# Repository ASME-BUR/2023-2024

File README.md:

# Bruin Underwater Robotics (2023-2024)
2023-2024 repository for ASME @ UCLA's Bruin Underwater Robotics Team

## Dependencies
Requires Ubuntu 22.04 + ROS2 Humble

Package dependencies:
- `controller`: `ros-<DISTRO>-control-toolbox`
- `eskf`: `ros-<DISTRO>-robot-localization`, `ros-<DISTRO>-mavros`
- `bur_auv`: `ros-<DISTRO>-navigation2`, `ros-<DISTRO>-behaviortree-cpp`
- `usb_camera_driver`: `ros-<DISTRO>-image-common`
- `drivers`: `pigpio`; see https://github.com/joan2937/pigpio/tree/master

This project contains the following Git submodules: 
- https://github.com/ASME-BUR/bur_rov_msgs
- https://github.com/micro-ROS/micro_ros_setup
- https://github.com/ptrmu/ros2_shared
- https://github.com/klintan/ros2_usb_camera

## Build Instructions
To build all packages: 
1. Install all dependencies: `sudo apt-get install <DEPENDENCIES>`

   i. Follow the instructions at https://github.com/joan2937/pigpio/tree/master for installing `pigpio`
3. Clone this repository: `git clone https://github.com/ASME-BUR/2023-2024.git`
4. Initialize Git submodules: `cd 2023-2024 && git submodule init && git submodule update`
5. Build ROS packages: `cd ros2_ws && colcon build --symlink-install`

## Run Instructions
To run as an AUV, run:
1. On Raspberry Pi (via SSH):

   i. Launch ROS nodes: `ros2 launch bur_rov rov.launch.py`
3. On Jetson Orin (via SSH):

   i. Launch ZED node: `ros2 launch bur_vision zed.launch.py`

   ii. Run YOLO: `ros2 run yolo yolo`

### Micro-Ros-Agent
To Run Micro-Ros-Agent separately, enter:

```
ros2 run micro_ros_agent micro_ros_agent serial --dev /dev/ttyACM0
```

- Serial indicates the transport type
- --dev is the port

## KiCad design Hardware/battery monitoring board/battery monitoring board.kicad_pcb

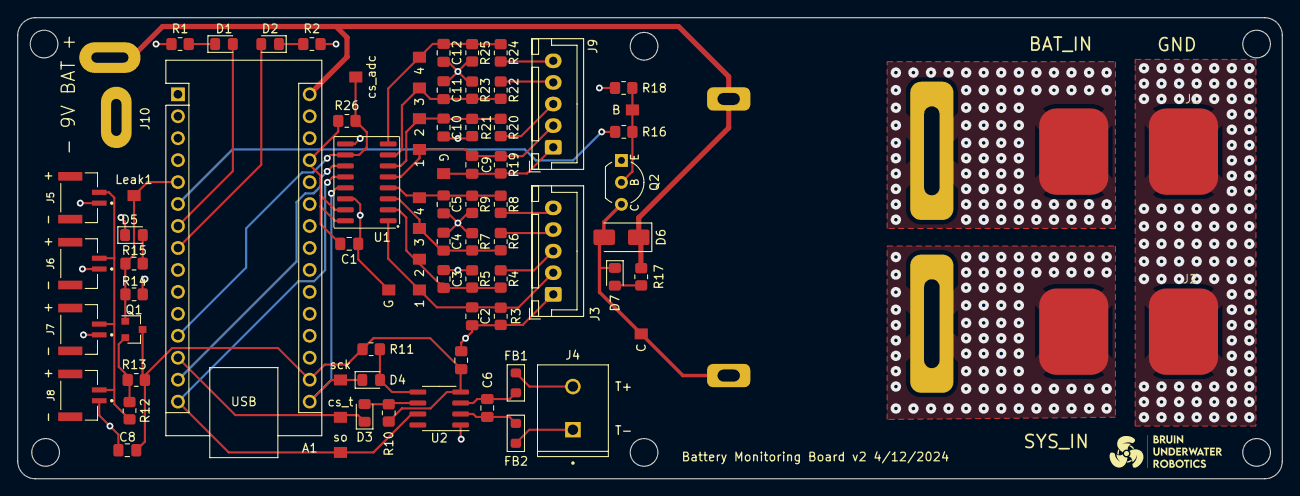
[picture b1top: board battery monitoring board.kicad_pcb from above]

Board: 2 copper layers, 146.3 x 53.3 mm, 80 parts (0 on the bottom side), 43 nets.

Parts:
3V7A1, 3V7B1, 7V4A1, 7V4B1, 11V1A1, 11V1B1, 14V8A1, 14V8B1: TestPoint; TestPoint_Pad_06
A1: Arduino_Nano_v3.x; Arduino_Nano
C1: 100nF; C_0805_2012Metric_Pad1.18x1.45mm_HandSolder
C2, C3, C4, C5, C9, C10, C11, C12: 10nF; C_0805_2012Metric_Pad1.18x1.45mm_HandSolder
C6: 0.01u; C_0805_2012Metric_Pad1.18x1.45mm_HandSolder
C7, C8: 10u; C_0805_2012Metric_Pad1.18x1.45mm_HandSolder
D1, D2: Green LED; D_0805_2012Metric_Pad1.15x1.40mm_HandSolder
D3, D4: D; D_0805_2012Metric_Pad1.15x1.40mm_HandSolder
D5, D7: LED; D_0805_2012Metric_Pad1.15x1.40mm_HandSolder
D6: 1N4007; D_SMA
FB1, FB2: FerriteBead; Ferrite_0805_2012Metric_Pad1.05x1.20mm_BigPads
J1, J2: Conn_01x02; Power Supply Pads
J3, J9: S5B-XH-A; JST_XH_B5B-XH-A_1x05_P2.50mm_Vertical
J4: Conn_01x02; TE_282836-2
J5, J6, J7, J8: Conn_01x02; JST_BM02B-GHS-TBT_LF__SN_
J10: - 9V BAT +; DEANS
K1: Relay_SPST-NO; Relay
Leak1: TestPoint; TestPoint_Pad_06
Q1: PNP; SOT-23
Q2: PN2222A; TO-92_Inline_Wide_EBC
R1, R2: 150; R_0805_2012Metric_Pad1.20x1.40mm_HandSolder
R3, R6, R19, R22: 20k; R_0805_2012Metric_Pad1.20x1.40mm_HandSolder
R4, R5, R7, R9, R10, R11, R20, R21, R23, R25, R26: 10k; R_0805_2012Metric_Pad1.20x1.40mm_HandSolder
R8, R24: 30k; R_0805_2012Metric_Pad1.20x1.40mm_HandSolder
R12, R14: 1k; R_0805_2012Metric_Pad1.20x1.40mm_HandSolder
R13: 27k; R_0805_2012Metric_Pad1.20x1.40mm_HandSolder
R15: 100; R_0805_2012Metric_Pad1.20x1.40mm_HandSolder
R16: 220; R_0805_2012Metric_Pad1.20x1.40mm_HandSolder
R17: 360; R_0805_2012Metric_Pad1.20x1.40mm_HandSolder
R18: 4.7k; R_0805_2012Metric_Pad1.20x1.40mm_HandSolder
TP1, TP2, TP4: TestPoint; TestPoint_Pad_06
U1: MCP3008; SOIC-16_3.9x9.9mm_P1.27mm
U2: MAX31855KASA; SOIC-8_3.9x4.9mm_P1.27mm
cs_adc1: TestPoint; TestPoint_Pad_06
cs_temp1: TestPoint; TestPoint_Pad_06
ground1: TestPoint; TestPoint_Pad_06
sck1: TestPoint; TestPoint_Pad_06
so1: TestPoint; TestPoint_Pad_06

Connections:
+3V3: A1.17 (3V3), C7.1, C8.1, Q1.3 (E), R10.2, R11.1, R13.1, U2.4 (V_CC)
+5V: A1.27 (+5V), C1.1, R26.2, U1.15 (Vref), U1.16 (Vdd)
+9V: A1.30 (VIN), D6.1 (K), J10.1, K1.A1, R17.1
/e-switch/BATTERY_IN: J1.2, K1.14
/e-switch/MCU_OUTPUT: A1.6 (D3), R16.1
/e-switch/SYSTEM_POWER: J2.1, K1.13
/leak sensor/LEAK_SIGNAL: A1.5 (D2), Leak1.1, Q1.1 (C), R14.1, R15.1
/leak sensor/PROBE: J5.2, J6.2, J7.2, J8.2, R12.1
/temp sensor/cs: A1.13 (D10), D3.1 (K), cs_temp1.1
/temp sensor/sck: A1.16 (D13), D4.1 (K), U1.13 (CLK), sck1.1
/temp sensor/so: A1.15 (D12), U1.12 (Dout), U2.7 (SO), so1.1
/voltage monitor2/7V4: J9.3, R20.2
/voltage monitor2/11V1: J9.4, R22.2
/voltage monitor2/14V8: J9.5, R24.2
/voltage monitor2/OUT1: 3V7B1.1, C9.1, J9.2, R19.1, U1.5 (CH4)
/voltage monitor2/OUT2: 7V4B1.1, C10.1, R20.1, R21.1, U1.6 (CH5)
/voltage monitor2/OUT3: 11V1B1.1, C11.1, R22.1, R23.1, U1.7 (CH6)
/voltage monitor2/OUT4: 14V8B1.1, C12.1, R24.1, R25.2, U1.8 (CH7)
/voltage monitor/7V4: J3.3, R4.2
/voltage monitor/11V1: J3.4, R6.2
/voltage monitor/14V8: J3.5, R8.2
/voltage monitor/OUT1: 3V7A1.1, C2.1, J3.2, R3.1, U1.1 (CH0)
/voltage monitor/OUT2: 7V4A1.1, C3.1, R4.1, R5.1, U1.2 (CH1)
/voltage monitor/OUT3: 11V1A1.1, C4.1, R6.1, R7.1, U1.3 (CH2)
/voltage monitor/OUT4: 14V8A1.1, C5.1, R8.1, R9.2, U1.4 (CH3)
GND: A1.4 (GND), A1.29 (GND), C1.2, C2.2, C3.2, C4.2, C5.2, C7.2, C8.2, C9.2, C10.2, C11.2, C12.2, D5.1 (K), J1.1, J2.2, J3.1, J5.1, J6.1, J7.1, J8.1, J9.1, J10.2, Q2.1 (E), R1.1, R2.1, R3.2, R5.2, R7.2, R9.1, R14.2, R18.2, R19.2, R21.2, R23.2, R25.1, TP4.1, U1.9 (DGND), U1.14 (AGND), U2.1 (GND), ground1.1
unnamed: A1.7 (D4), D1.2 (A)
unnamed: A1.8 (D5), D2.2 (A)
unnamed: A1.12 (D9), R26.1, U1.10 (~CS/SHDN), cs_adc1.1
unnamed: A1.14 (D11), U1.11 (Din)
unnamed: D1.1 (K), R1.2
unnamed: D2.1 (K), R2.2
unnamed: D3.2 (A), R10.1, U2.6 (~CS)
unnamed: D4.2 (A), R11.2, U2.5 (SCK)
unnamed: D5.2 (A), R15.2
unnamed: D6.2 (A), D7.1 (K), K1.A2, Q2.3 (C), TP2.1
unnamed: D7.2 (A), R17.2
unnamed: FB2.1, J4.1
unnamed: FB1.1, J4.2
unnamed: Q1.2 (B), R12.2, R13.2
unnamed: Q2.2 (B), R16.2, R18.1, TP1.1
unnamed: C6.1, FB1.2, U2.3 (T+)
unnamed: C6.2, FB2.2, U2.2 (T-)

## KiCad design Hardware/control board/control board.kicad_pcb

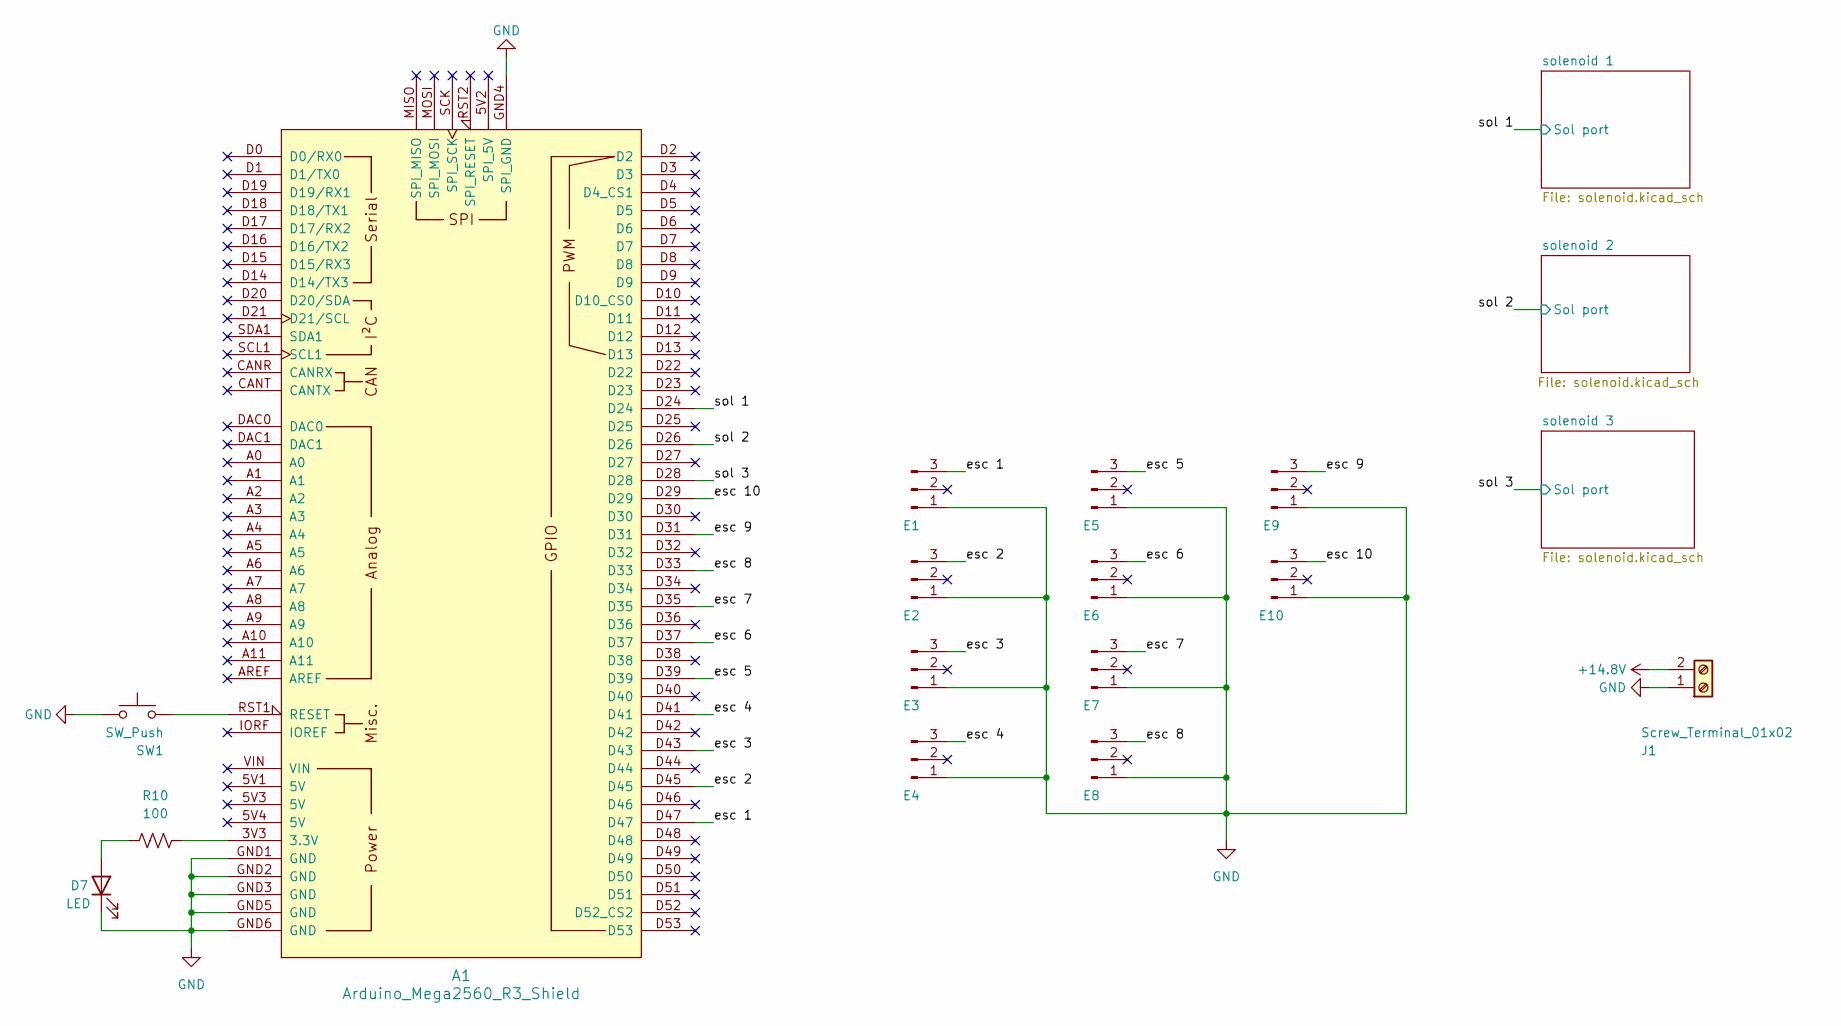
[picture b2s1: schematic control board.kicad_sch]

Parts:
A1: Arduino_Mega2560_R3_Shield; Arduino_Due_Shield
D7: LED; LED_D3.0mm_Clear
E1, E2, E3, E4, E5, E6, E7, E8, E9, E10: Conn_01x03_Pin; PinHeader_1x03_P2.54mm_Vertical
J1: Screw_Terminal_01x02; TE_282836-2
R10: 100; R_0805_2012Metric
SW1: SW_Push; SW_PUSH_6mm

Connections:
+14.8V: J1.2; also elsewhere on the board
/esc 1: A1.D47, E1.3
/esc 2: A1.D45, E2.3
/esc 3: A1.D43, E3.3
/esc 4: A1.D41, E4.3
/esc 5: A1.D39, E5.3
/esc 6: A1.D37, E6.3
/esc 7: A1.D35, E7.3
/esc 8: A1.D33, E8.3
/esc 9: A1.D31, E9.3
/esc 10: A1.D29, E10.3
/sol 1: A1.D24; also elsewhere on the board
/sol 2: A1.D26; also elsewhere on the board
/sol 3: A1.D28; also elsewhere on the board
GND: A1.GND1 (GND), A1.GND2 (GND), A1.GND3 (GND), A1.GND4 (SPI_GND), A1.GND5 (GND), A1.GND6 (GND), D7.1 (K), E1.1, E2.1, E3.1, E4.1, E5.1, E6.1, E7.1, E8.1, E9.1, E10.1, J1.1, SW1.1; also elsewhere on the board
unnamed: A1.3V3 (3.3V), R10.2
unnamed: A1.RST1 (RESET), SW1.2
unnamed: D7.2 (A), R10.1

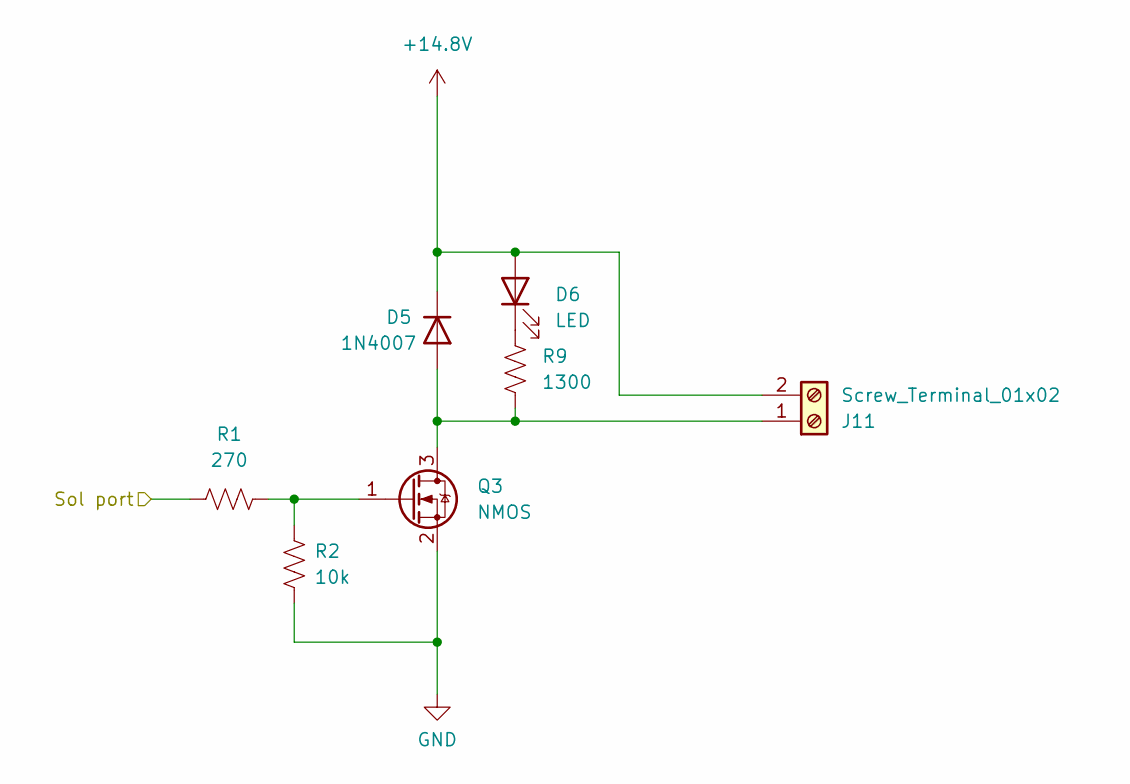
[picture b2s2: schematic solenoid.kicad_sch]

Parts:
D5: 1N4007; D_DO-41_SOD81_P10.16mm_Horizontal
D6: LED; LED_D3.0mm
J11: Screw_Terminal_01x02; TE_282836-2
Q3: NMOS; SOT-23
R1: 270; R_0805_2012Metric
R2: 10k; R_0805_2012Metric
R9: 1300; R_0805_2012Metric

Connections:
+14.8V: D5.1 (K), D6.2 (A), J11.2; also elsewhere on the board
/sol 1: R1.1; also elsewhere on the board
GND: Q3.2 (S), R2.2; also elsewhere on the board
unnamed: D5.2 (A), J11.1, Q3.3 (D), R9.2
unnamed: D6.1 (K), R9.1

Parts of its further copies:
D1, D3: 1N4007; D_DO-41_SOD81_P10.16mm_Horizontal
D2, D4: LED; LED_D3.0mm
J9, J10: Screw_Terminal_01x02; TE_282836-2
Q1, Q2: NMOS; SOT-23
R3, R7: 270; R_0805_2012Metric
R4, R8: 10k; R_0805_2012Metric
R5, R6: 1300; R_0805_2012Metric

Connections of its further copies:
+14.8V: D1.1 (K), D2.2 (A), D3.1 (K), D4.2 (A), J9.2, J10.2; also elsewhere on the board
/sol 2: R3.1; also elsewhere on the board
/sol 3: R7.1; also elsewhere on the board
GND: Q1.2 (S), Q2.2 (S), R4.2, R8.2; also elsewhere on the board
unnamed: D1.2 (A), J9.1, Q1.3 (D), R5.2
unnamed: D2.1 (K), R5.1
unnamed: D3.2 (A), J10.1, Q2.3 (D), R6.2
unnamed: D4.1 (K), R6.1
unnamed: Q2.1 (G), R3.2, R4.1

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
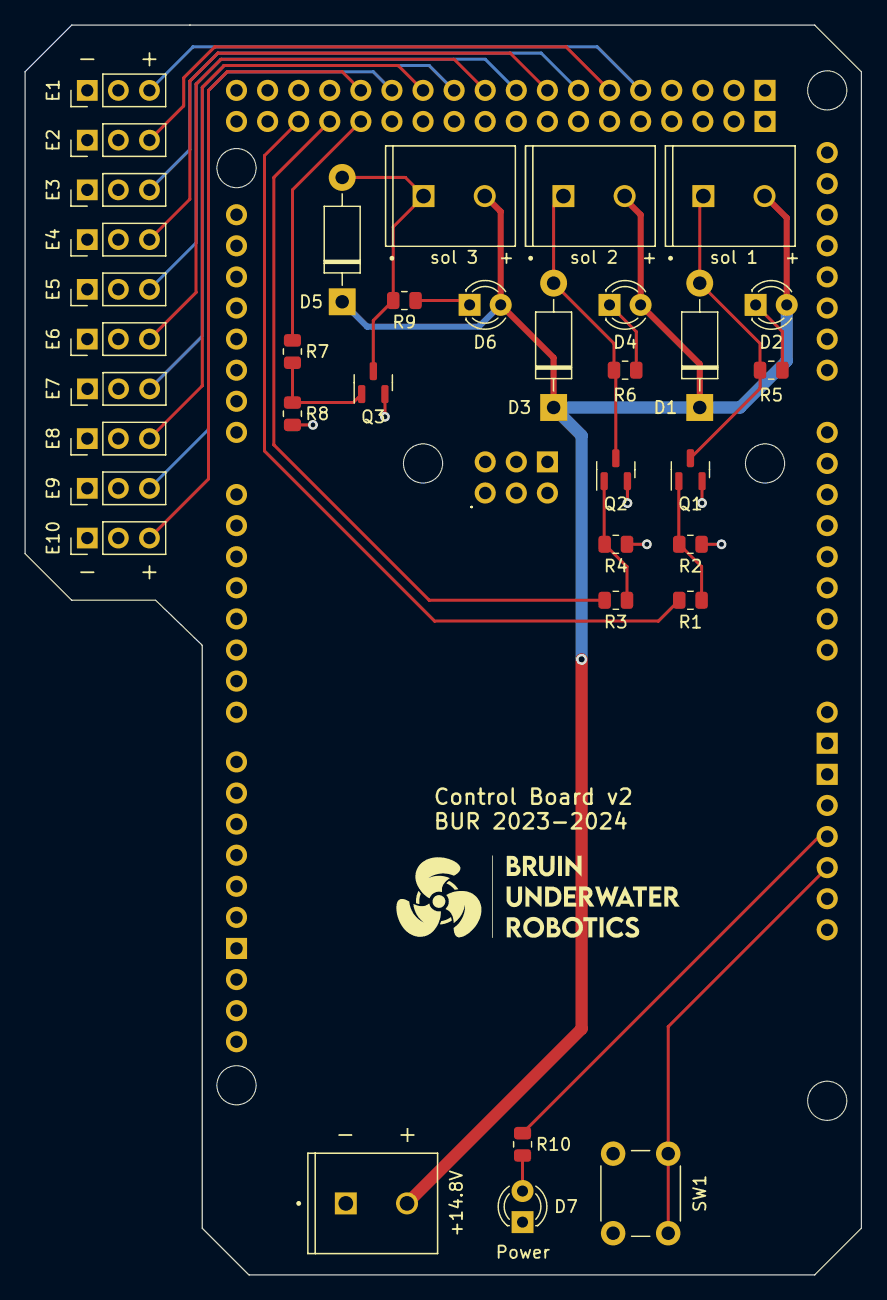
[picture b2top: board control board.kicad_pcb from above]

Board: 2 copper layers, 68.3 x 102.1 mm, 36 parts (0 on the bottom side), 27 nets.

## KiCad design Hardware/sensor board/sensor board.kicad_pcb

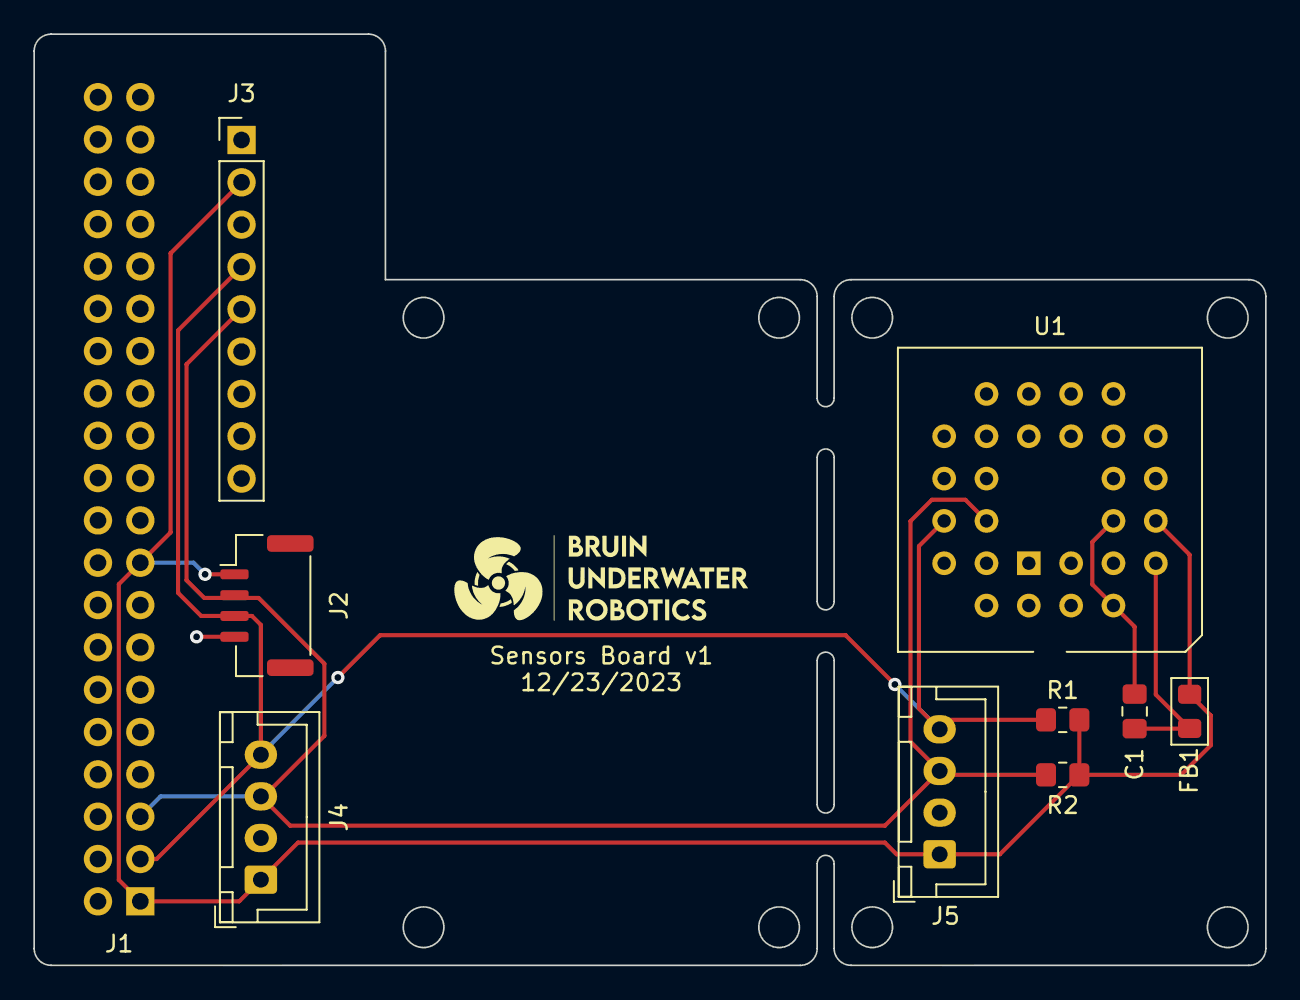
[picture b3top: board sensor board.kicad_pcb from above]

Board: 2 copper layers, 73.9 x 55.9 mm, 10 parts (1 on the bottom side), 5 nets.

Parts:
C1: 470nF; C_0805_2012Metric_Pad1.18x1.45mm_HandSolder
FB1: 600R@100MHz, 200mA; Ferrite_0805_2012Metric_Pad1.15x1.40mm_BigPads
J1: Raspberry_Pi_2_3; PinSocket_2x20_P2.54mm_Vertical
J2: Bar30; JST_GH_BM04B-GHS-TBT_1x04-1MP_P1.25mm_Vertical
J3: LPS331AP; PinHeader_1x09_P2.54mm_Vertical
J4, J5: Conn_01x04_Pin; JST_XH_B4B-XH-A_1x04_P2.50mm_Vertical
R1, R2: 2.7k; R_0805_2012Metric_Pad1.20x1.40mm_HandSolder
U1: MTi_3; PLCC-28_THT-Socket

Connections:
+3.3V: FB1.1, J1.1 (3V3), J1.17 (3V3), J2.1 (3.3V), J3.2 (VIN), J4.1, J5.1, R1.2, R2.2, U1.7 (VDDIO)
/SCL: J1.5 (SCL/GPIO3), J2.2 (SCL), J3.5 (SCL), J4.3, J5.3, R2.1, U1.24 (I2C_SCL)
/SDA: J1.3 (SDA/GPIO2), J2.3 (SDA), J3.4 (SDA), J4.4, J5.4, R1.1, U1.23 (I2C_SDA)
GND: C1.1, J1.6 (GND), J1.9 (GND), J1.14 (GND), J1.20 (GND), J1.25 (GND), J1.30 (GND), J1.34 (GND), J1.39 (GND), J2.4 (GND), J3.3 (GND), J4.2, J5.2, U1.4 (GND), U1.8 (GND), U1.13 (GND), U1.25 (GND)
unnamed: C1.2, FB1.2, U1.5 (VDDA)

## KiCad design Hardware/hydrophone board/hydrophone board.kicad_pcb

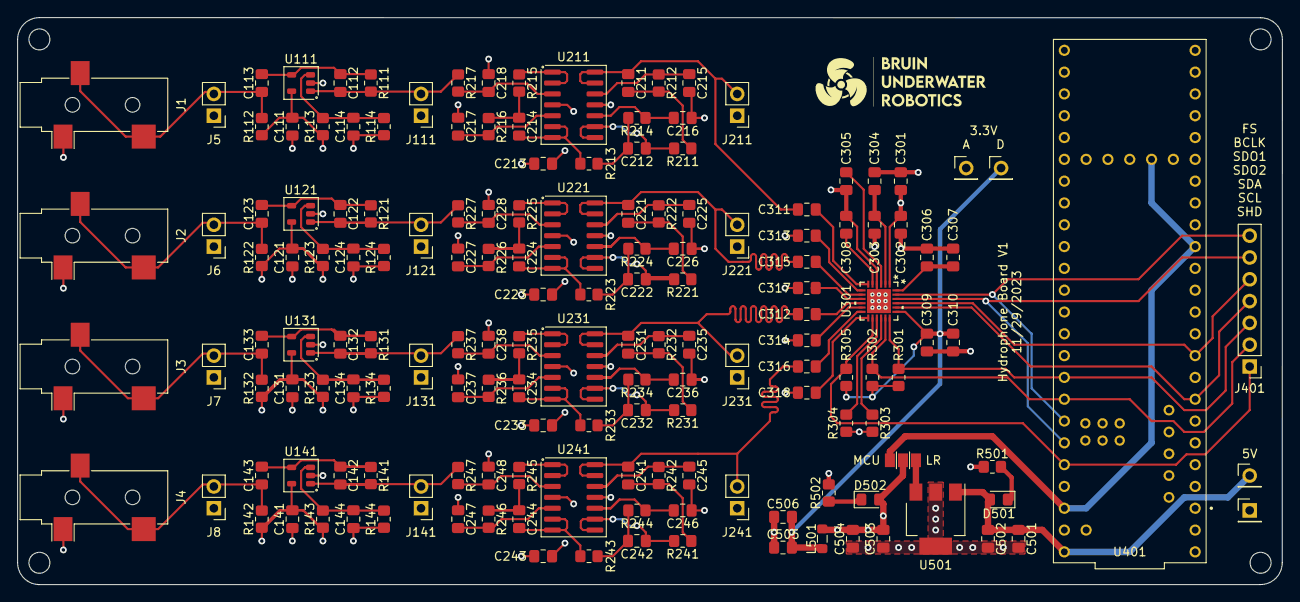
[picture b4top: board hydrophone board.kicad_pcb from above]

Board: 4 copper layers, 147.3 x 66.0 mm, 159 parts (0 on the bottom side), 89 nets.

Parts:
C111, C121, C131, C141, C213, C223, C233, C243, C301, C303, C306, C309: 0.1u; C_0805_2012Metric_Pad1.18x1.45mm_HandSolder
C112, C122, C132, C142: 820p; C_0805_2012Metric_Pad1.18x1.45mm_HandSolder
C113, C123, C133, C143: 6.8u; C_0805_2012Metric_Pad1.18x1.45mm_HandSolder
C114, C124, C134, C144, C302, C305, C308, C311, C312, C313, C314, C315, C316, C317, C318, C501, C504, C506: 1u; C_0805_2012Metric_Pad1.18x1.45mm_HandSolder
C211, C212, C214, C218, C221, C222, C224, C228, C231, C232, C234, C238, C241, C242, C244, C248: 360p; C_0805_2012Metric_Pad1.18x1.45mm_HandSolder
C215, C216, C225, C226, C235, C236, C245, C246: 36p; C_0805_2012Metric_Pad1.18x1.45mm_HandSolder
C217, C227, C237, C247: 18p; C_0805_2012Metric_Pad1.18x1.45mm_HandSolder
C304, C307, C310: 10u; C_0805_2012Metric_Pad1.18x1.45mm_HandSolder
C502, C503, C505: 22u; C_0805_2012Metric_Pad1.18x1.45mm_HandSolder
D501, D502: LED; LED_0805_2012Metric_Pad1.15x1.40mm_HandSolder
J1, J2, J3, J4: AudioJack3_Ground; Jack_3.5mm_CUI_SJ-3523-SMT_Horizontal
J5, J6, J7, J8, J111, J121, J131, J141, J211, J221, J231, J241: Conn_01x02; PinHeader_1x02_P2.54mm_Vertical
J401: Conn_01x07; PinHeader_1x07_P2.54mm_Vertical
JP501: Jumper_3_Bridged12; JUMPER_SMD_1x3
L501: 600R @ 100MHz; L_0805_2012Metric_Pad1.05x1.20mm_HandSolder
R111, R121, R131, R141: 715; R_0805_2012Metric_Pad1.20x1.40mm_HandSolder
R112, R122, R132, R142: 360; R_0805_2012Metric_Pad1.20x1.40mm_HandSolder
R113, R114, R123, R124, R133, R134, R143, R144: 10k; R_0805_2012Metric_Pad1.20x1.40mm_HandSolder
R211, R221, R231, R241: 5.62k; R_0805_2012Metric_Pad1.20x1.40mm_HandSolder
R212, R222, R232, R242: 169k; R_0805_2012Metric_Pad1.20x1.40mm_HandSolder
R213, R223, R233, R243: 8.45k; R_0805_2012Metric_Pad1.20x1.40mm_HandSolder
R214, R224, R234, R244: 115k; R_0805_2012Metric_Pad1.20x1.40mm_HandSolder
R215, R216, R225, R226, R235, R236, R245, R246: 44.2k; R_0805_2012Metric_Pad1.20x1.40mm_HandSolder
R217, R227, R237, R247: 9.76k; R_0805_2012Metric_Pad1.20x1.40mm_HandSolder
R301, R302: 2.2k; R_0805_2012Metric_Pad1.20x1.40mm_HandSolder
R303, R304, R305: 1k; R_0805_2012Metric_Pad1.20x1.40mm_HandSolder
R501, R502: 470; R_0805_2012Metric_Pad1.20x1.40mm_HandSolder
TP501, TP502, TP503, TP504: TestPoint_Probe; PinHeader_1x01_P2.54mm_Vertical
U111, U121, U131, U141: AD8541ARTZ; SOT-23-5
U211, U221, U231, U241: AD8648ARZ; SOIC-14_3.9x8.7mm_P1.27mm
U301: XLV320ADC5140IRTWR; RTW24_4P15X4P15_TEX
U401: DEV-16771; MODULE_DEV-16771
U501: LT1963AxST-3.3; SOT-223-3_TabPin2

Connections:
+3.3VA: C111.1, C121.1, C131.1, C141.1, C213.1, C223.1, C233.1, C243.1, C301.1, C302.1, C503.1, C504.1, D502.2 (A), JP501.2 (C), L501.1, R112.2, R113.1, R122.2, R123.1, R132.2, R133.1, R142.2, R143.1, TP502.1, U111.5 (V+), U121.5 (V+), U131.5 (V+), U141.5 (V+), U211.4 (V+), U221.4 (V+), U231.4 (V+), U241.4 (V+), U301.1 (AVDD)
+3.3VD: C309.1, C310.1, C505.1, C506.1, L501.2, R301.1, R302.1, R305.1, TP503.1, U301.19 (IOVDD)
+5V: C501.1, C502.1, D501.2 (A), TP501.1, U401.VIN, U501.1 (IN)
/IN_1: C113.1, J1.R, J1.T, J5.2, R112.1
/IN_1_A: C112.1, J111.2, R111.2, R217.1, U111.1
/IN_1_B: C211.1, C311.1, J211.2, U211.13 (-), U211.14
/IN_2: C123.1, J2.R, J2.T, J6.2, R122.1
/IN_2_A: C122.1, J121.2, R121.2, R227.1, U121.1
/IN_2_B: C221.1, C315.1, J221.2, U221.13 (-), U221.14
/IN_3: C133.1, J3.R, J3.T, J7.2, R132.1
/IN_3_A: C132.1, J131.2, R131.2, R237.1, U131.1
/IN_3_B: C231.1, C312.1, J231.2, U231.13 (-), U231.14
/IN_4: C143.1, J4.R, J4.T, J8.2, R142.1
/IN_4_A: C142.1, J141.2, R141.2, R247.1, U141.1
/IN_4_B: C241.1, C316.1, J241.2, U241.13 (-), U241.14
/adc/ADDR0: R303.2, U301.16 (ADDR0_SCLK)
/adc/ADDR1: R304.1, U301.15 (ADDR1_MISO)
/adc/BCLK: J401.6, U301.22 (BCLK), U401.21 (A7)
/adc/FSYNC: J401.7, U301.23 (FSYNC), U401.20 (A6)
/adc/IN1M: C313.2, U301.7 (IN1M_GPO1)
/adc/IN1P: C311.2, U301.6 (IN1P_GPI1)
/adc/IN2M: C317.2, U301.9 (IN2M_GPO2)
/adc/IN2P: C315.2, U301.8 (IN2P_GPI2)
/adc/IN3M: C314.2, U301.11 (IN3M_GPO3)
/adc/IN3P: C312.2, U301.10 (IN3P_GPI3)
/adc/IN4M: C318.2, U301.13 (IN4M_GPO4)
/adc/IN4P: C316.2, U301.12 (IN4P_GPI4)
/adc/SCL: J401.2, R302.2, U301.17 (SCL_MOSI), U401.19 (A5)
/adc/SDA: J401.3, R301.2, U301.18 (SDA_SSZ), U401.18 (A4)
/adc/SDOUT: J401.5, U301.21 (SDOUT), U401.8 (TX2)
/adc/SDOUT_2: J401.4, U301.20 (GPIO1), U401.6 (OUT1D)
/adc/SHDNZ: J401.1, R305.2, U301.14 (SHDNZ), U401.22 (A8)
/mcu/3.3V MCU: JP501.3 (B), U401.3.3V_1 (3.3V), U401.3.3V_2 (3.3V), U401.3.3V_3 (3.3V)
GND: C111.2, C114.1, C121.2, C124.1, C131.2, C134.1, C141.2, C144.1, C213.2, C215.1, C216.1, C217.1, C218.1, C223.2, C225.1, C226.1, C227.1, C228.1, C233.2, C235.1, C236.1, C237.1, C238.1, C243.2, C245.1, C246.1, C247.1, C248.1, C301.2, C302.2, C303.2, C304.2, C305.2, C306.2, C307.2, C308.2, C309.2, C310.2, C313.1, C314.1, C317.1, C318.1, C501.2, C502.2, C503.2, C504.2, C505.2, C506.2, J1.S, J2.S, J3.S, J4.S, J5.1, J6.1, J7.1, J8.1, J111.1, J121.1, J131.1, J141.1, J211.1, J221.1, J231.1, J241.1, R114.2, R124.2, R134.2, R144.2, R303.1, R304.2, R501.2, R502.2, TP504.1, U111.2 (V-), U121.2 (V-), U131.2 (V-), U141.2 (V-), U211.11 (V-), U221.11 (V-), U231.11 (V-), U241.11 (V-), U301.4 (AVSS), U301.25 (EPAD), U401.GND1 (GND), U401.GND2 (GND), U401.GND3 (GND), U401.GND4 (GND), U401.GND5 (GND), U401.USB_GND1 (USB_GND), U401.USB_GND2 (USB_GND), U501.2 (GND)
unnamed: C211.2, R211.2, R212.1
unnamed: C212.2, R213.2, R214.1
unnamed: C214.2, R215.2, R216.1
unnamed: C221.2, R221.2, R222.1
unnamed: C222.2, R223.2, R224.1
unnamed: C224.2, R225.2, R226.1
unnamed: C231.2, R231.2, R232.1
unnamed: C232.2, R233.2, R234.1
unnamed: C234.2, R235.2, R236.1
unnamed: C241.2, R241.2, R242.1
unnamed: C242.2, R243.2, R244.1
unnamed: C244.2, R245.2, R246.1
unnamed: D501.1 (K), R501.1
unnamed: D502.1 (K), R502.1
unnamed: JP501.1 (A), U501.3 (OUT)
unnamed: C114.2, R113.2, R114.1, U111.3 (+)
unnamed: C112.2, C113.2, R111.1, U111.4 (-)
unnamed: C124.2, R123.2, R124.1, U121.3 (+)
unnamed: C122.2, C123.2, R121.1, U121.4 (-)
unnamed: C134.2, R133.2, R134.1, U131.3 (+)
unnamed: C132.2, C133.2, R131.1, U131.4 (-)
unnamed: C144.2, R143.2, R144.1, U141.3 (+)
unnamed: C142.2, C143.2, R141.1, U141.4 (-)
unnamed: C218.2, R217.2, U211.3 (+)
unnamed: R215.1, U211.1, U211.2 (-)
unnamed: C217.2, R216.2, U211.5 (+)
unnamed: C214.1, R213.1, U211.6 (-), U211.7
unnamed: C216.2, R214.2, U211.10 (+)
unnamed: C212.1, R211.1, U211.8, U211.9 (-)
unnamed: C215.2, R212.2, U211.12 (+)
unnamed: C228.2, R227.2, U221.3 (+)
unnamed: R225.1, U221.1, U221.2 (-)
unnamed: C227.2, R226.2, U221.5 (+)
unnamed: C224.1, R223.1, U221.6 (-), U221.7
unnamed: C226.2, R224.2, U221.10 (+)
unnamed: C222.1, R221.1, U221.8, U221.9 (-)
unnamed: C225.2, R222.2, U221.12 (+)
unnamed: C238.2, R237.2, U231.3 (+)
unnamed: R235.1, U231.1, U231.2 (-)
unnamed: C237.2, R236.2, U231.5 (+)
unnamed: C234.1, R233.1, U231.6 (-), U231.7
unnamed: C236.2, R234.2, U231.10 (+)
unnamed: C232.1, R231.1, U231.8, U231.9 (-)
unnamed: C235.2, R232.2, U231.12 (+)
unnamed: C248.2, R247.2, U241.3 (+)
unnamed: R245.1, U241.1, U241.2 (-)
unnamed: C247.2, R246.2, U241.5 (+)
unnamed: C244.1, R243.1, U241.6 (-), U241.7
unnamed: C246.2, R244.2, U241.10 (+)
unnamed: C242.1, R241.1, U241.8, U241.9 (-)
unnamed: C245.2, R242.2, U241.12 (+)
unnamed: C303.1, C304.1, U301.2 (AREG)
unnamed: C306.1, C307.1, U301.24 (DREG)
unnamed: C308.1, U301.5 (MICBIAS)
unnamed: C305.1, U301.3 (VREF)

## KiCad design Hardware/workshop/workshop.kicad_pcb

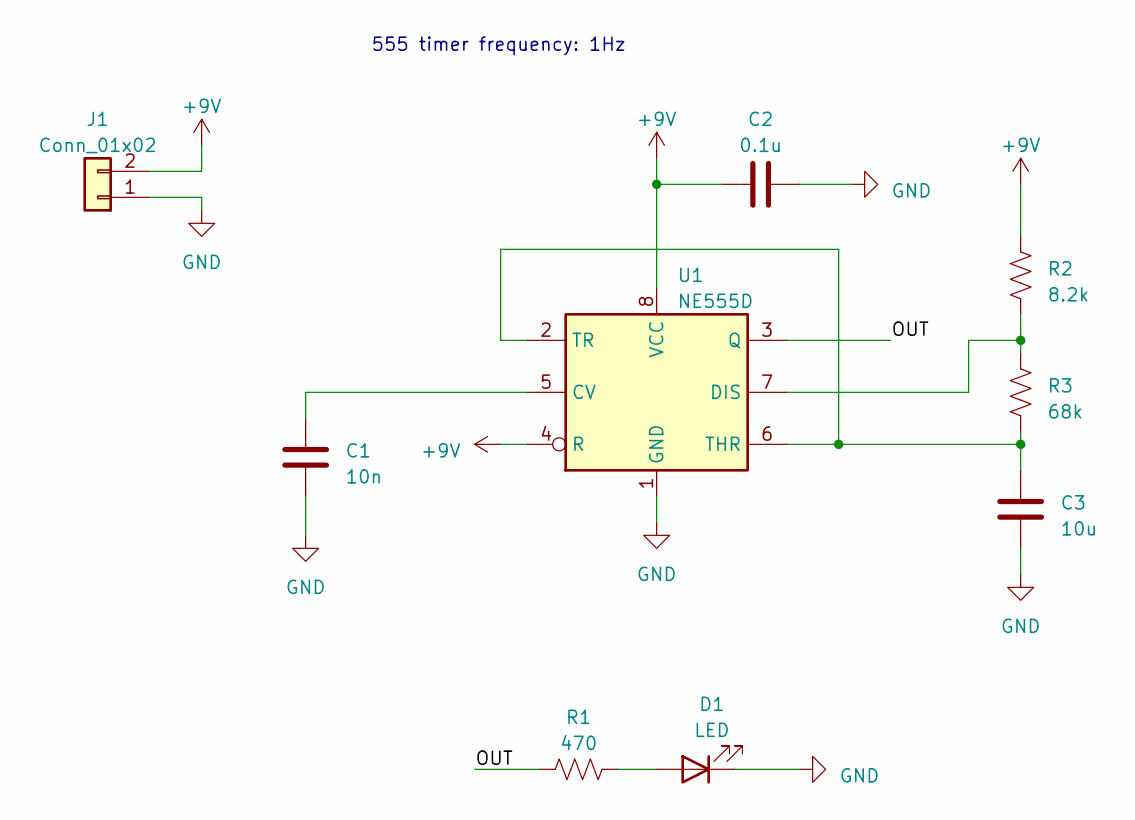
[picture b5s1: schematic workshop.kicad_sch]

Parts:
C1: 10n; C_0805_2012Metric
C2: 0.1u; C_0805_2012Metric
C3: 10u; C_0805_2012Metric
D1: LED; LED_D3.0mm
J1: Conn_01x02; JST_XH_B2B-XH-A_1x02_P2.50mm_Vertical
R1: 470; R_0805_2012Metric
R2: 8.2k; R_0805_2012Metric
R3: 68k; R_0805_2012Metric
U1: NE555D; SOIC-8_3.9x4.9mm_P1.27mm

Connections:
+9V: C2.1, J1.2, R2.1, U1.4 (R), U1.8 (VCC)
/OUT: R1.1, U1.3 (Q)
GND: C1.1, C2.2, C3.1, D1.1 (K), J1.1, U1.1 (GND)
unnamed: D1.2 (A), R1.2
unnamed: C1.2, U1.5 (CV)
unnamed: R2.2, R3.1, U1.7 (DIS)
unnamed: C3.2, R3.2, U1.2 (TR), U1.6 (THR)

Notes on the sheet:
555 timer frequency: 1Hz

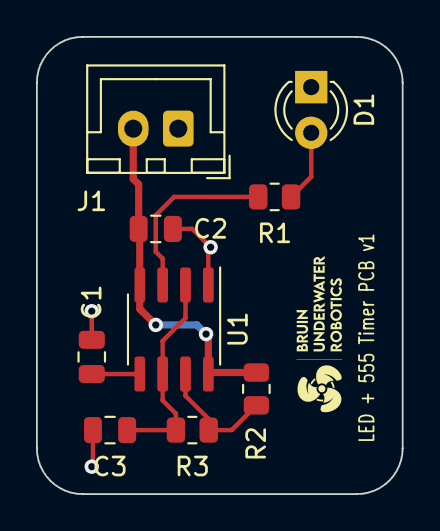
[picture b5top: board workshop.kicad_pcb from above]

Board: 2 copper layers, 20.3 x 25.4 mm, 9 parts (0 on the bottom side), 7 nets.

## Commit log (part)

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2023-12-02 added tags on scrw terminals + logo
2023-12-06 Added screw holes + other stuff
2023-12-06 Added traces pt.I
2023-12-09 Added traces pt.II
2023-12-16 more pcb work
2023-12-16 cleaned up traces
2023-12-16 control board clean up
2023-12-17 changed led footprint to 0805
2023-12-17 updated pcb
2023-12-17 layout for sensor board
2023-12-20 fixed nmos footprint
2023-12-20 trace + fill zone adjustments
2023-12-20 changed pnp footprint
2023-12-22 control board gerber
2023-12-23 updated outlines(needs ground plane)
2023-12-23 added gnd plane
2023-12-23 connected Vin to 9V battery
2023-12-24 modified traces + screw hole positions, added silkscreen
2023-12-24 silkscreen
2023-12-25 gerbers
2023-12-25 fixed rpi header orientation
2024-01-13 cleanup summer
2024-01-13 cleanup teensy
2024-01-13 create teensy project
2024-01-13 init(), setActive(), setSleep() functions
2024-01-13 Initial commit: barebones B-Tree
    Added package containing a barebones behavior tree implementation using BehaviorTree_CPP
2024-01-20 read and write func
2024-01-20 remove teensy
2024-01-20 added audio input/output data channel initialization functions & single/multi byte read functions
2024-01-27 "cross corr"
2024-02-03 init functions added to main
2024-02-04 micro-ros agent setup
2024-02-04 fix accidental push
2024-02-10 some reorganizing
2024-02-10 joystick
2024-02-10 Naming changes + tweaked axis assignment
2024-02-13 humble
2024-02-13 link to fork
2024-02-13 add gitignore
2024-02-15 fix cmake
2024-02-17 add submodule
2024-02-24 fix read
2024-02-24 imu code
2024-02-24 Update ESKF to fixed version for ROS2
2024-02-24 pid controller
2024-02-26 cleanup
2024-03-02 fixed read/write issue where bits weren't being saved by registers
2024-03-02 Initial Subscriber C Code
    Added initial custom message subscriber code, commented for easy reading
    May need updates depending on how we want to handle the custom message.
2024-03-02 Fix build issues
    Added additional dependencies & lines to CMakeList, package.xml to fix build issues
2024-03-02 Fix controller node parameters & node
    Fixed controller node naming being invalid
    Fixed controller parameter definitions not matching intended parameter types
2024-03-02 Added ESKF, controller to workspace
2024-03-05 custom msg
2024-03-05 add extra packages
2024-03-06 tested thruster node
2024-03-06 edit gitignore
2024-03-06 Added pose listener + master ROV launch file
2024-03-06 add submodules
2024-03-06 remove Plankton
2024-03-06 cleanup and editing joy_command
2024-03-07 fix imu publisher
2024-03-07 move summer files
2024-03-07 moved summer files to new branch
2024-03-07 Revert "move summer files"
    This reverts commit dcc654c4dfa420283e55fadc02be0fd5f4214d46.
2024-03-07 Revert "cleanup and editing joy_command"
    This reverts commit 2e6e25b8e937d4ac6cd896f990b1f9f7233a2138.
2024-03-07 move summer elsewhere
2024-03-07 move Summer
2024-03-07 thruster manager
2024-03-07 fix things idk what
2024-03-07 fix pin numbers
2024-03-07 add launch file
2024-03-07 fix arduino pins
2024-03-07 edit joy_command
2024-03-07 edit launch files
2024-03-07 change messages
2024-03-07 joy commmand takes angular vel
2024-03-07 include a bunch of stuff
2024-03-07 Uploaded Arduino code
2024-03-07 make sure everything communicates
2024-03-07 add uros
2024-03-07 remove install build
2024-03-07 remove BUR_ROV
2024-03-07 arduino serial checks
2024-03-08 fix arduino
2024-03-08 change motor assignments
2024-03-09 pid active mode
2024-03-09 thruster testing
2024-03-09 edit thruster config
2024-03-09 updated arduino code
2024-03-11 reassign arduino pins
2024-03-12 joystick axis mapping parameter
2024-03-12 joy target orientation
2024-03-12 Fixed Arduino issues + redid thruster mappings
2024-03-18 boost arduino publish rate to 30
2024-04-01 corrected pin headers and LED resistors
    fixed pin headers and LED resistors
2024-04-02 imu data rate boosted to the moon
2024-04-02 minor changes
2024-04-03 solenoids somewhat
2024-04-03 fix 9 motors
2024-04-03 add .pio
2024-04-03 remove .pio
2024-04-03 Added adc to schematic
2024-04-03 change motor pin to 4
2024-04-03 zed day before pool test 1 vision
2024-04-03 git ignore
2024-04-03 ignore build install log
2024-04-03 remove cached dir
2024-04-03 cached test
2024-04-03 test auth jetson
2024-04-03 REVERT test auth
2024-04-04 Remove joy.launch from rov.launch
2024-04-04 depth sensor
2024-04-04 move controller to bur_rov_control
2024-04-04 velocity integrator
2024-04-04 add accel due to gravity offset
2024-04-06 updated PCB layout
2024-04-06 rearranged parts
2024-04-06 visualization stuff
2024-04-06 remove aruco
2024-04-06 updated Board design to v2
2024-04-06 fix imu and add debug
2024-04-09 added offset for zed? Need to check coor system definition is consistent
2024-04-09 launch file use in README
2024-04-09 typo
2024-04-09 fixed monki offset
2024-04-09 update eskf
2024-04-10 Added micro_ros launch file [untested]
2024-04-10 change param to arg in micro ros launch
2024-04-10 move eskf into bur_auv
2024-04-10 update links
2024-04-10 rename folder
2024-04-10 change usb port
2024-04-10 imu fix and pid shutoff
2024-04-11 barsensor changes
2024-04-11 fix static transform
2024-04-11 updated battery board pt.II
2024-04-11 reviewed erc
2024-04-12 erc-clear battery board
2024-04-12 cleaned up schematic
2024-04-12 layout cleanup
2024-04-12 final design check
2024-04-12 added silkscreen
2024-04-12 updated battery pcb (voltage dividers etc)
2024-04-13 fixed github problems
2024-04-13 change coords
2024-04-13 Gravity adjustment for joy_command acceleration
2024-04-13 flip cam
2024-04-13 Changed initialization for gravity offset
2024-04-13 finalized battery board !!
2024-04-13 resolved erc/drc issues
2024-04-13 final finalization
2024-04-15 usb camera and thruster manager fix
2024-04-16 change camera id
2024-04-16 Revert "Merge branch 'vision' into beta"
    This reverts commit f1e6420afb077450be450b1f17c6219170e716e2, reversing
    changes made to a562868834bc5c2841ddd2bde647c6d3720ce0a3.
2024-04-20 Pitch/roll coefficients
2024-04-20 Update bur_nodes.h
    Added bools, NodeStatuses, and Points for each of the major tasks
2024-04-20 Update bur_test.cpp
    Registering new task nodes
2024-04-20 arduino timestamp sync
2024-04-25 depth and orientation hold
2024-04-25 depth sensor and build error fix
2024-04-27 cleanup pid
2024-04-27 fix minor error
2024-04-27 robot localization changes
2024-04-30 eskf changes
2024-04-30 removed unneeded topics hopefully doesnt break
2024-04-30 nakool soda reviews
2024-04-30 code cleanup and fixes
2024-04-30 pid fixes
2024-04-30 imu reset orientation and frame id
2024-05-01 disable vel control need to fix logic
2024-05-04 start TF n added zed imu back
2024-05-04 EKF launch & params
2024-05-04 revert
2024-05-04 removed tutorials
2024-05-04 reverted poop
2024-05-04 added adc code to arduino folder
2024-05-04 reorganize ekf and add depth sensor
2024-05-11 ignore pt and almost done yolo node
2024-05-11 need to fix ekf frames
2024-05-14 change launch
2024-05-14 arduino merge code
2024-05-15 somewhat stable ekf and minor fixes
2024-05-15 verbose output launch arg
2024-05-15 ekf finally hopefully maybe
2024-05-16 thruster matrix generator
2024-05-19 path planning
2024-05-21 change joystick config and incorporate ekf
2024-05-21 change custom msgs to submodule for platformio
2024-05-22 change extra_packages
2024-05-22 need testing, deleted .pio folder
2024-05-25 Add Orca4 submodules
2024-05-25 Moved Orca4 submodules to new ros2_ws/src/submodules directory
2024-05-25 Add BehaviorTree.CPP submodule
2024-05-25 Removed eskf
2024-05-25 Removed BehaviorTree.CPP submodule
    [I forgot it is installed by default along with Navigation2]
2024-05-25 Added behavior tree planner under bur_auv/bur_auv_planner
2024-05-25 set pose and twist
2024-05-25 joy command tested
2024-05-30 Added test mode to thruster_manager
    Added boolean flag to thruster_manager; maps motors to buttons [instead of based on coeffs] if true
2024-05-30 Revised thruster matrix generator
    Changed order of thrusters to (hopefully correctly) match code motor numbering
    Fixed rotational axis order mismatch in output
    Also fixed error in thruster_manager test mode
2024-06-01 verified joy and pid directions
2024-06-01 change baud rate for micro ros
2024-06-01 correct pid outputs
2024-06-01 Revised bur_auv_planner
    Rewrote bur_auv_planner to track target locations
    Added new behavior tree for prequalification testing
2024-06-01 Make Nav2 nodes autostart
    Flipped Orca parameter to make Nav2 nodes autostart
    Added parameter for bt_navigator odom topic
    Removed unused lines
2024-06-01 Added flag to change source for controller twist setpoint
2024-06-02 Behavior tree fixes, part 1/?
2024-06-03 fix thruster directions
2024-06-03 new launch files
2024-06-03 update dependencies
2024-06-03 fix auv launch file
2024-06-04 6/03 pool test behavior tree changes
2024-07-13 summer 1
2024-07-14 untested 3d segment
2024-07-14 labels, cord = results ValueError: not enough values to unpack (expected 2, got 0)
2024-07-28 remove .pio folder
2024-07-30 Update README.md
    Added package dependencies
2024-08-03 straight-line planner
2024-08-03 Initial behavior tree manager
2024-08-04 WIP example
2024-08-06 Behavior tree go-forward test
2024-08-06 Behavior tree fixes
2024-08-06 First working behavior tree
2024-08-06 Gate, target positions as ROS params
2024-08-06 pool test night, position control still kinda wonky
2024-08-06 remove orca4
2024-08-06 Manager auto-shutdown on behavior tree end as ROS param
2024-08-06 weightsss
2024-08-06 Separate UpdateTarget/GoToTarget BT nodes
2024-08-06 open loop
2024-08-06 Behavior tree cleanup
2024-08-06 fixes
2024-08-07 launch files for tomorrow
2024-08-07 only activate pid if bot is in water
2024-08-07 make orientation relative
2024-08-07 Torpedo BT node stub
2024-08-07 Qualified
2024-08-08 change coordinate system of robot to be x-forward
2024-08-08 fixed publishing
2024-08-08 readme
2024-08-08 weights update
2024-08-08 flipped depth sensor
2024-08-08 Added combined message publisher [untested]
2024-08-08 weights rename
2024-08-08 Fix bug
2024-08-08 Test OpenCV YOLO viewer
2024-08-08 fix build
2024-08-08 Add yolo_msgs
2024-08-09 velocity control
2024-08-09 gains
2024-08-09 Fleshed out comp behavior tree
2024-08-09 fix error
2024-08-09 Fix behavior tree segfault
2024-08-09 open loop 08/08
2024-08-09 pool test 0808
2024-08-09 WIP behavior tree expansion
2024-08-09 depth stuff
2024-08-09 orientation control
2024-08-09 Behavior tree orientation position control test
2024-08-09 Publish odometry
2024-08-09 Wait-until-underwater as ROS param
2024-08-10 TurnToOrientation type
2024-08-10 arduino merge node kinda complete but imu is not updating
2024-08-10 Non-vision behavior tree
2024-08-10 fix thruster button mapping
2024-08-10 Minor adjustments
2024-08-10 Comp lane D behavior tree changes
2024-08-10 Node params as behavior tree ports
2024-08-10 modify open_loop
2024-10-15 Commit comp changes
2024-10-15 Final comp commit (from Pi)
